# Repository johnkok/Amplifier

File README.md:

# Amplifier
This is an amplifier project, inluding both software sources for CPU/DSP and also hardware design files.

# folders
**fw:** includes the ST32F407 CPU firmware<br />
**DSP:** includes the ADAU1497 design files<br />
**amp_board:** includes the kicad design foles for the audio power amplifier board<br />
**cntrl_board:** includes the controller board kicad design files<br />
**3d:** 3d printer freecad files<br />

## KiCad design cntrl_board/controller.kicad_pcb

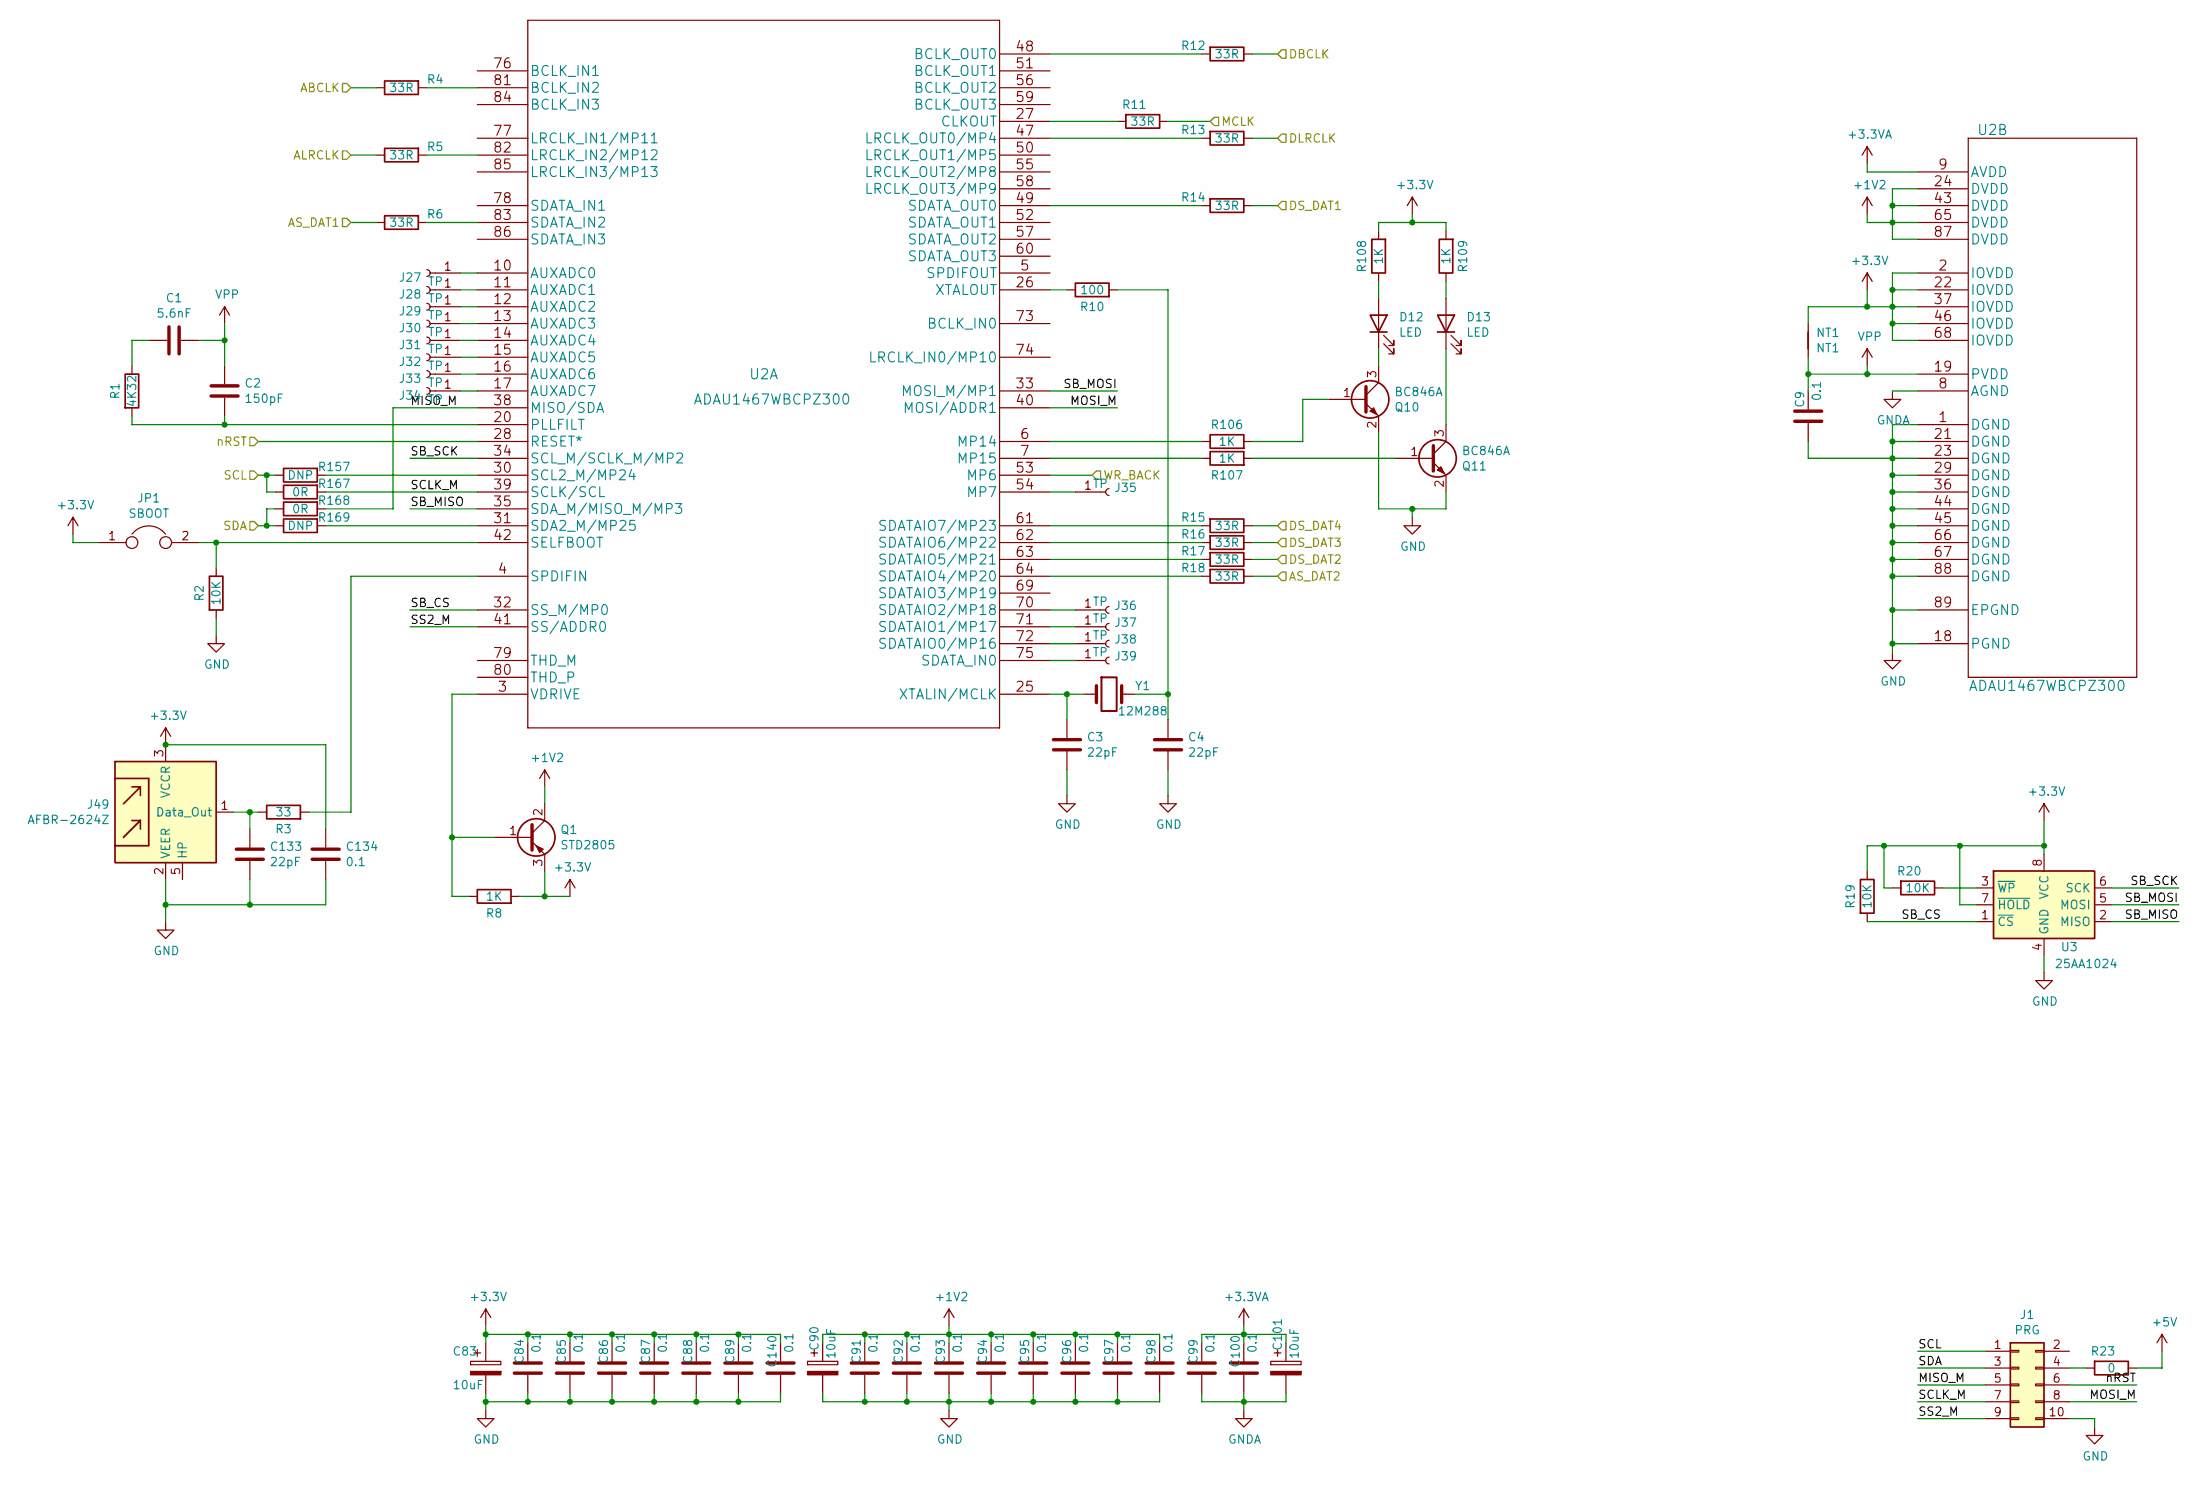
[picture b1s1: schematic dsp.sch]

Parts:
C1: 5.6nF; C_0603_1608Metric_Pad1.08x0.95mm_HandSolder
C2: 150pF; C_0603_1608Metric_Pad1.08x0.95mm_HandSolder
C3, C4, C133: 22pF; C_0603_1608Metric_Pad1.08x0.95mm_HandSolder
C9, C84, C85, C86, C87, C88, C89, C91, C92, C93, C94, C95, C96, C97, C98, C99, C100, C134, C140: 0.1; C_0603_1608Metric_Pad1.08x0.95mm_HandSolder
C83, C90, C101: 10uF; CP_Elec_5x5.8
D12, D13: LED; LED_0603_1608Metric_Pad1.05x0.95mm_HandSolder
J1: PRG; IDC-Header_2x05_P2.54mm_Vertical
J27, J28, J29, J30, J31, J32, J33, J34, J35, J36, J37, J38, J39: TP; TestPoint_Keystone_5000-5004_Miniature
J49: AFBR-2624Z; TOSLINK
JP1: SBOOT; PinHeader_1x02_P2.54mm_Vertical
NT1: NT1; NetTie-2_SMD_Pad0.5mm
Q1: STD2805; TO-252-3_TabPin2
Q10, Q11: BC846A; SOT-23
R1: 4K32; R_0603_1608Metric_Pad0.98x0.95mm_HandSolder
R2, R19, R20: 10K; R_0603_1608Metric_Pad0.98x0.95mm_HandSolder
R3: 33; R_0603_1608Metric_Pad0.98x0.95mm_HandSolder
R4, R5, R6, R11, R12, R13, R14, R15, R16, R17, R18: 33R; R_0603_1608Metric_Pad0.98x0.95mm_HandSolder
R8, R106, R107, R108, R109: 1K; R_0603_1608Metric_Pad0.98x0.95mm_HandSolder
R10: 100; R_0603_1608Metric_Pad0.98x0.95mm_HandSolder
R23: 0; R_0603_1608Metric_Pad0.98x0.95mm_HandSolder
R157, R169: DNP; R_0603_1608Metric_Pad0.98x0.95mm_HandSolder
R167, R168: 0R; R_0603_1608Metric_Pad0.98x0.95mm_HandSolder
U2: ADAU1467WBCPZ300
U3: 25AA1024; SOIJ-8_5.3x5.3mm_P1.27mm
Y1: 12M288; Crystal_HC49-U_Vertical

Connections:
+1V2: C90.1, C91.1, C92.1, C93.1, C94.1, C95.1, C96.1, C97.1, C98.1, Q1.2 (C), U2.24 (DVDD), U2.43 (DVDD), U2.65 (DVDD), U2.87 (DVDD)
+3.3VA: C99.1, C100.1, C101.1, U2.9 (AVDD); also elsewhere on the board
+5V: R23.1; also elsewhere on the board
/codec/ABCLK: R4.1; also elsewhere on the board
/codec/ALRCLK: R5.1; also elsewhere on the board
/codec/AS_DAT1: R6.1; also elsewhere on the board
/codec/AS_DAT2: R18.1; also elsewhere on the board
/codec/DBCLK: R12.1; also elsewhere on the board
/codec/DLRCLK: R13.1; also elsewhere on the board
/codec/DS_DAT1: R14.1; also elsewhere on the board
/codec/DS_DAT2: R17.1; also elsewhere on the board
/codec/DS_DAT3: R16.1; also elsewhere on the board
/codec/DS_DAT4: R15.1; also elsewhere on the board
/codec/MCLK: R11.1; also elsewhere on the board
/codec/nRST: J1.6, U2.28 (RESET*); also elsewhere on the board
/dsp/MISO_M: J1.5, R168.2, U2.38 (MISO/SDA)
/dsp/MOSI_M: J1.8, U2.40 (MOSI/ADDR1)
/dsp/SB_CS: R19.2, U2.32 (SS_M/MP0), U3.1 (~CS)
/dsp/SB_MISO: U2.35 (SDA_M/MISO_M/MP3), U3.2 (MISO)
/dsp/SB_MOSI: U2.33 (MOSI_M/MP1), U3.5 (MOSI)
/dsp/SB_SCK: U2.34 (SCL_M/SCLK_M/MP2), U3.6 (SCK)
/dsp/SCLK_M: J1.7, R167.2, U2.39 (SCLK/SCL)
/dsp/SS2_M: J1.9, U2.41 (SS/ADDR0)
/dsp/WR_BACK: U2.53 (MP6); also elsewhere on the board
/ucu/DSP_SCL: J1.1, R157.1, R167.1; also elsewhere on the board
/ucu/DSP_SDA: J1.3, R168.1, R169.1; also elsewhere on the board
GND: C3.2, C4.2, C9.2, C83.2, C84.2, C85.2, C86.2, C87.2, C88.2, C89.2, C90.2, C91.2, C92.2, C93.2, C94.2, C95.2, C96.2, C97.2, C98.2, C133.2, C134.2, C140.2, J1.10, J49.2 (VEER), Q10.2 (E), Q11.2 (E), R2.2, U2.1 (DGND), U2.18 (PGND), U2.21 (DGND), U2.23 (DGND), U2.29 (DGND), U2.36 (DGND), U2.44 (DGND), U2.45 (DGND), U2.66 (DGND), U2.67 (DGND), U2.88 (DGND), U2.89 (EPGND), U3.4 (GND); also elsewhere on the board
GNDA: C99.2, C100.2, C101.2, U2.8 (AGND); also elsewhere on the board
unnamed: C1.1, R1.1
unnamed: C2.1, R1.2, U2.20 (PLLFILT)
unnamed: C3.1, U2.25 (XTALIN/MCLK), Y1.1
unnamed: C4.1, R10.2, Y1.2
unnamed: C133.1, J49.1 (Data_Out), R3.1
unnamed: D12.1 (K), Q10.3 (C)
unnamed: D12.2 (A), R108.1
unnamed: D13.1 (K), Q11.3 (C)
unnamed: D13.2 (A), R109.1
unnamed: J1.4, R23.2
unnamed: J27.1, U2.10 (AUXADC0)
unnamed: J28.1, U2.11 (AUXADC1)
unnamed: J29.1, U2.12 (AUXADC2)
unnamed: J30.1, U2.13 (AUXADC3)
unnamed: J31.1, U2.14 (AUXADC4)
unnamed: J32.1, U2.15 (AUXADC5)
unnamed: J33.1, U2.16 (AUXADC6)
unnamed: J34.1, U2.17 (AUXADC7)
unnamed: J35.1, U2.54 (MP7)
unnamed: J36.1, U2.70 (SDATAIO2/MP18)
unnamed: J37.1, U2.71 (SDATAIO1/MP17)
unnamed: J38.1, U2.72 (SDATAIO0/MP16)
unnamed: J39.1, U2.75 (SDATA_IN0)
unnamed: JP1.2, R2.1, U2.42 (SELFBOOT)
unnamed: Q1.1 (B), R8.1, U2.3 (VDRIVE)
unnamed: Q10.1 (B), R106.2
unnamed: Q11.1 (B), R107.2
unnamed: R3.2, U2.4 (SPDIFIN)
unnamed: R4.2, U2.81 (BCLK_IN2)
unnamed: R5.2, U2.82 (LRCLK_IN2/MP12)
unnamed: R6.2, U2.83 (SDATA_IN2)
unnamed: R10.1, U2.26 (XTALOUT)
unnamed: R11.2, U2.27 (CLKOUT)
unnamed: R12.2, U2.48 (BCLK_OUT0)
unnamed: R13.2, U2.47 (LRCLK_OUT0/MP4)
unnamed: R14.2, U2.49 (SDATA_OUT0)
unnamed: R15.2, U2.61 (SDATAIO7/MP23)
unnamed: R16.2, U2.62 (SDATAIO6/MP22)
unnamed: R17.2, U2.63 (SDATAIO5/MP21)
unnamed: R18.2, U2.64 (SDATAIO4/MP20)
unnamed: R20.1, U3.3 (~WP)
unnamed: R106.1, U2.6 (MP14)
unnamed: R107.1, U2.7 (MP15)
unnamed: R157.2, U2.30 (SCL2_M/MP24)
unnamed: R169.2, U2.31 (SDA2_M/MP25)
VPP: C1.2, C2.2, C9.1, NT1.1, U2.19 (PVDD)

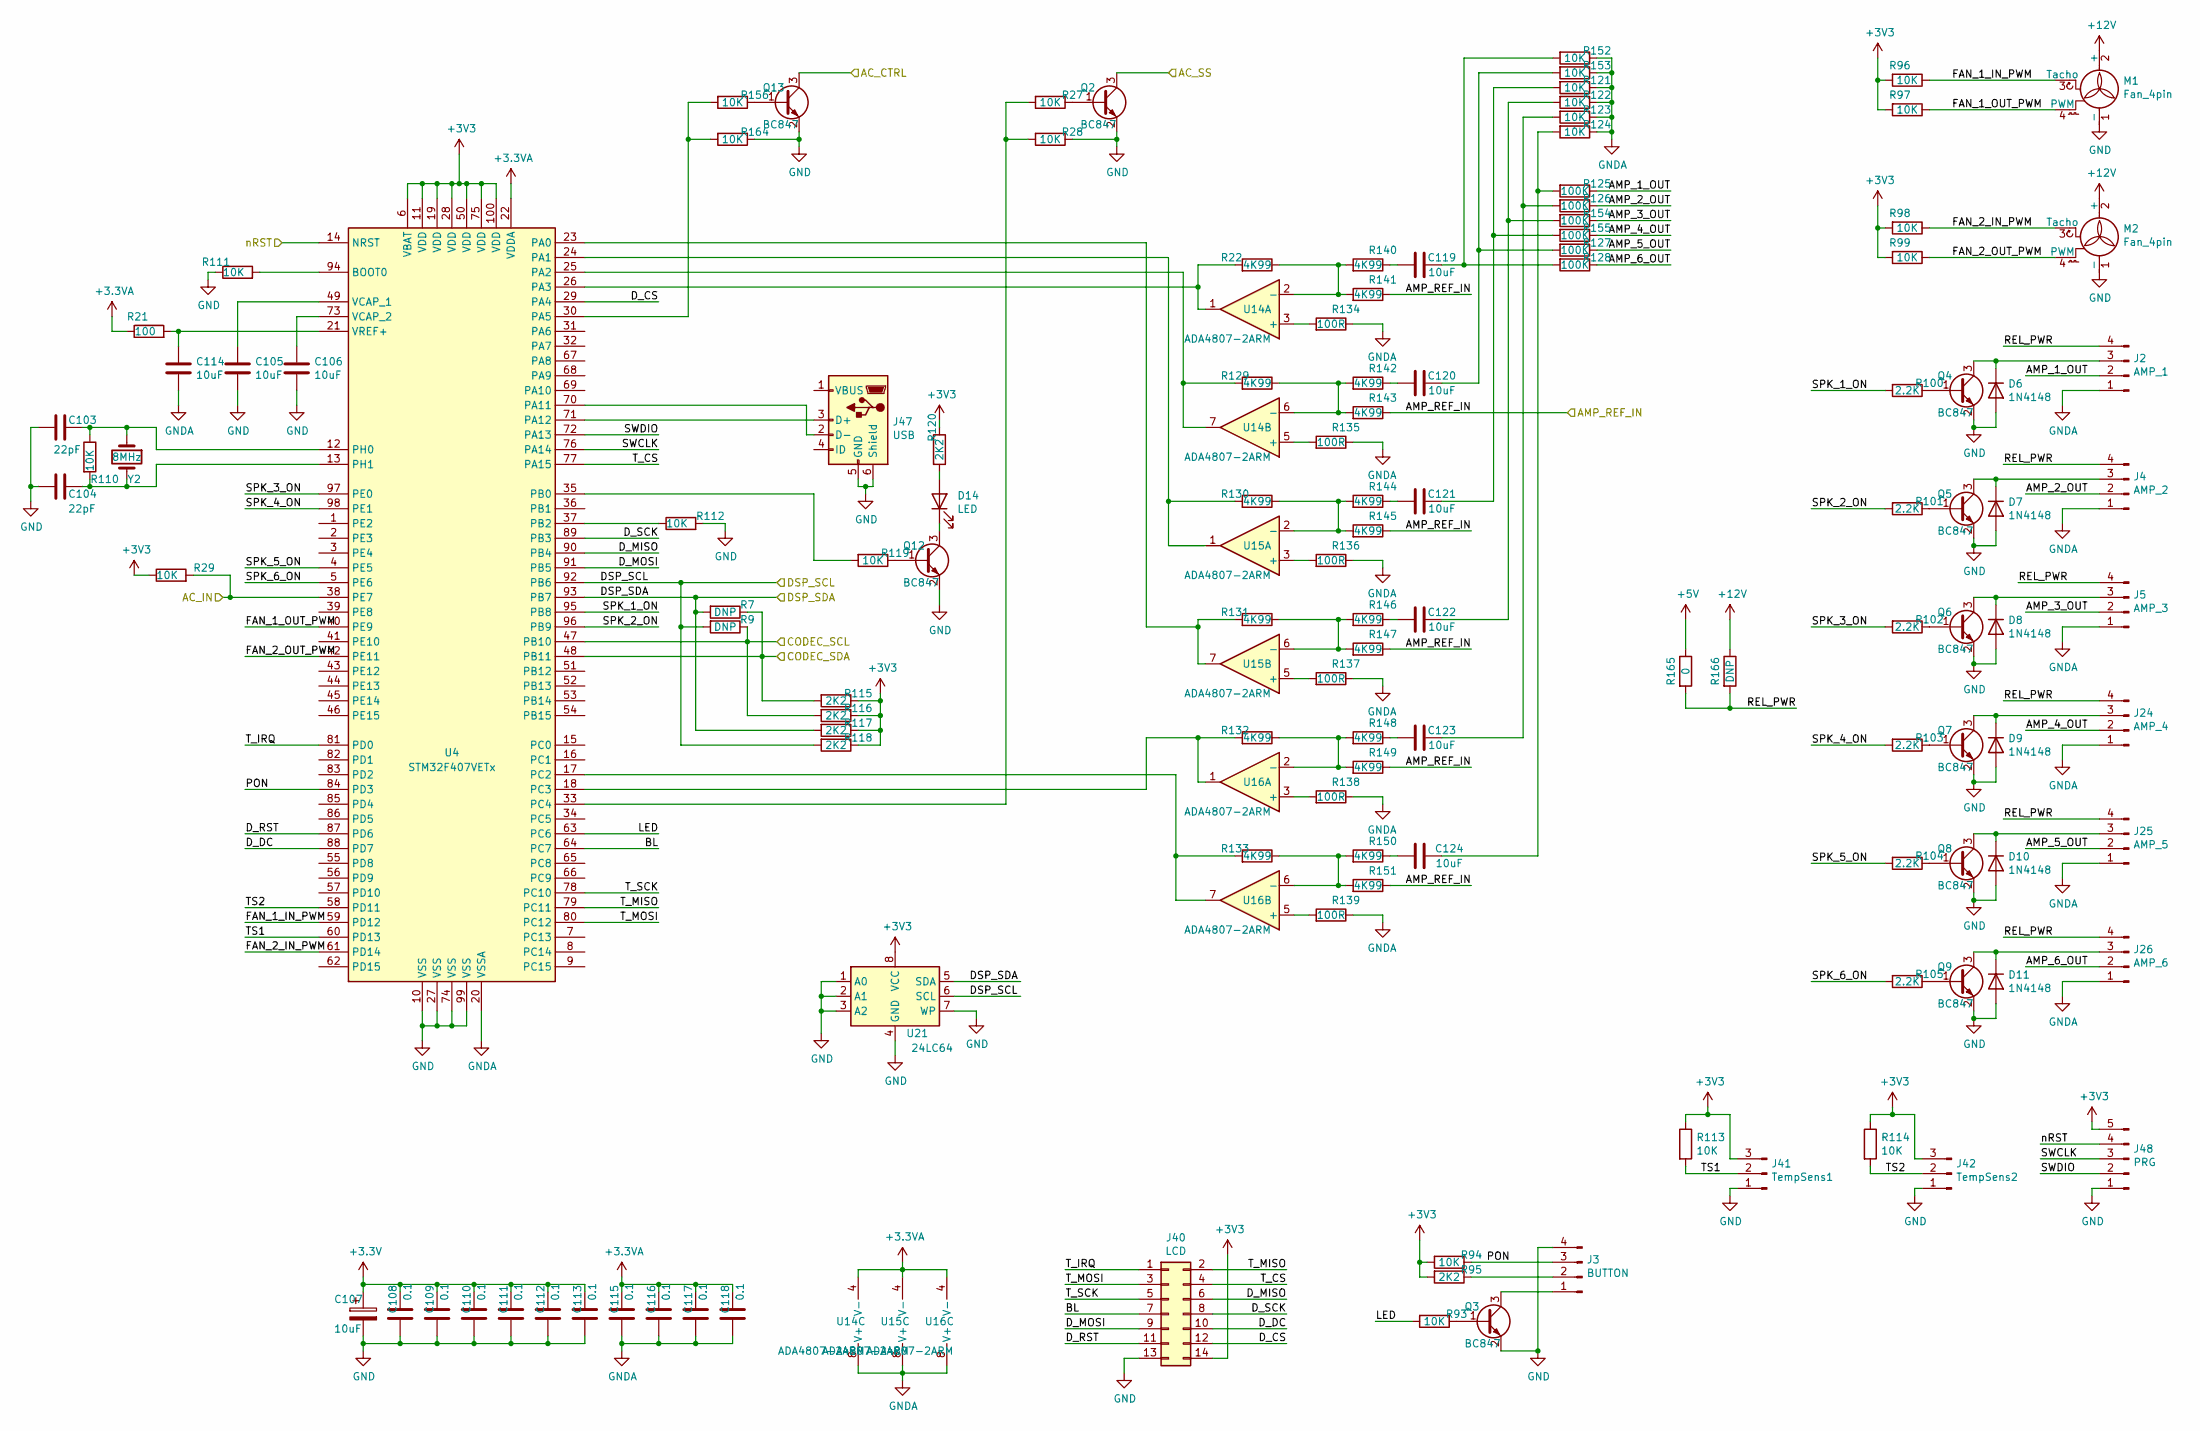
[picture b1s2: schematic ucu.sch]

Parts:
C103, C104: 22pF; R_0603_1608Metric_Pad0.98x0.95mm_HandSolder
C105, C106, C114, C119, C120, C121, C122, C123, C124: 10uF; C_0805_2012Metric_Pad1.18x1.45mm_HandSolder
C107: 10uF; CP_Elec_5x5.8
C108, C109, C110, C111, C112, C113, C115, C116, C117, C118: 0.1; C_0603_1608Metric_Pad1.08x0.95mm_HandSolder
D6, D7, D8, D9, D10, D11: 1N4148; D_SOD-323_HandSoldering
D14: LED; LED_0603_1608Metric_Pad1.05x0.95mm_HandSolder
J2: AMP_1; PinHeader_1x04_P1.27mm_Vertical
J3: BUTTON; PinHeader_1x04_P2.54mm_Vertical
J4: AMP_2; PinHeader_1x04_P1.27mm_Vertical
J5: AMP_3; PinHeader_1x04_P1.27mm_Vertical
J24: AMP_4; PinHeader_1x04_P1.27mm_Vertical
J25: AMP_5; PinHeader_1x04_P1.27mm_Vertical
J26: AMP_6; PinHeader_1x04_P1.27mm_Vertical
J40: LCD; PinSocket_2x07_P2.54mm_Vertical
J41: TempSens1; PinHeader_1x03_P2.54mm_Vertical
J42: TempSens2; PinHeader_1x03_P2.54mm_Vertical
J47: USB; USB_Micro-B_Molex-105017-0001
J48: PRG; PinSocket_1x05_P2.54mm_Vertical
M1, M2: Fan_4pin; PinHeader_1x04_P2.54mm_Vertical
Q2, Q3, Q4, Q5, Q6, Q7, Q8, Q9, Q12, Q13: BC847; SOT-23
R7, R9: DNP; R_0603_1608Metric_Pad0.98x0.95mm_HandSolder
R21: 100; R_0603_1608Metric_Pad0.98x0.95mm_HandSolder
R22, R129, R130, R131, R132, R133, R140, R141, R142, R143, R144, R145, R146, R147, R148, R149, R150, R151: 4K99; R_0603_1608Metric_Pad0.98x0.95mm_HandSolder
R27, R28, R29, R93, R94, R96, R97, R98, R99, R110, R111, R112, R113, R114, R119, R121, R122, R123, R124, R152, R153, R156, R164: 10K; R_0603_1608Metric_Pad0.98x0.95mm_HandSolder
R95, R115, R116, R117, R118, R120: 2K2; R_0603_1608Metric_Pad0.98x0.95mm_HandSolder
R100, R101, R102, R103, R104, R105: 2.2K; R_0603_1608Metric_Pad0.98x0.95mm_HandSolder
R125, R126, R127, R128, R154, R155: 100K; R_0603_1608Metric_Pad0.98x0.95mm_HandSolder
R134, R135, R136, R137, R138, R139: 100R; R_0603_1608Metric_Pad0.98x0.95mm_HandSolder
R165: 0; R_1206_3216Metric_Pad1.30x1.75mm_HandSolder
R166: DNP; R_1206_3216Metric_Pad1.30x1.75mm_HandSolder
U4: STM32F407VETx; LQFP-100_14x14mm_P0.5mm
U14, U15, U16: ADA4807-2ARM; MSOP-8_3x3mm_P0.65mm
U21: 24LC64; SO-8_3.9x4.9mm_P1.27mm
Y2: 8MHz; Crystal_HC49-4H_Vertical

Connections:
+3.3VA: C115.1, C116.1, C117.1, C118.1, R21.1, U4.22 (VDDA), U14.4 (V-), U15.4 (V-), U16.4 (V-); also elsewhere on the board
+5V: R165.1; also elsewhere on the board
+12V: M1.2 (+), M2.2 (+), R166.1; also elsewhere on the board
/codec/AMP_REF_IN: R141.1, R143.1, R145.1, R147.1, R149.1, R151.1; also elsewhere on the board
/codec/nRST: J48.4, U4.14 (NRST); also elsewhere on the board
/ucu/AC_CTRL: Q13.3 (C); also elsewhere on the board
/ucu/AC_IN: R29.2, U4.38 (PE7); also elsewhere on the board
/ucu/AC_SS: Q2.3 (C); also elsewhere on the board
/ucu/AMP_1_OUT: J2.2, R125.1
/ucu/AMP_2_OUT: J4.2, R126.1
/ucu/AMP_3_OUT: J5.2, R154.1
/ucu/AMP_4_OUT: J24.2, R155.1
/ucu/AMP_5_OUT: J25.2, R127.1
/ucu/AMP_6_OUT: J26.2, R128.1
/ucu/BL: J40.7, U4.64 (PC7)
/ucu/CODEC_SCL: R9.1, R116.2, U4.47 (PB10); also elsewhere on the board
/ucu/CODEC_SDA: R7.1, R115.2, U4.48 (PB11); also elsewhere on the board
/ucu/DSP_SCL: R9.2, R118.2, U4.92 (PB6), U21.6 (SCL); also elsewhere on the board
/ucu/DSP_SDA: R7.2, R117.2, U4.93 (PB7), U21.5 (SDA); also elsewhere on the board
/ucu/D_CS: J40.12, U4.29 (PA4)
/ucu/D_DC: J40.10, U4.88 (PD7)
/ucu/D_MISO: J40.6, U4.90 (PB4)
/ucu/D_MOSI: J40.9, U4.91 (PB5)
/ucu/D_RST: J40.11, U4.87 (PD6)
/ucu/D_SCK: J40.8, U4.89 (PB3)
/ucu/FAN_1_IN_PWM: M1.3 (Tacho), R96.1, U4.59 (PD12)
/ucu/FAN_1_OUT_PWM: M1.4 (PWM), R97.1, U4.40 (PE9)
/ucu/FAN_2_IN_PWM: M2.3 (Tacho), R98.1, U4.61 (PD14)
/ucu/FAN_2_OUT_PWM: M2.4 (PWM), R99.1, U4.42 (PE11)
/ucu/LED: R93.2, U4.63 (PC6)
/ucu/PON: J3.3, R94.1, U4.84 (PD3)
/ucu/REL_PWR: J2.4, J4.4, J5.4, J24.4, J25.4, J26.4, R165.2, R166.2
/ucu/SPK_1_ON: R100.2, U4.95 (PB8)
/ucu/SPK_2_ON: R101.2, U4.96 (PB9)
/ucu/SPK_3_ON: R102.2, U4.97 (PE0)
/ucu/SPK_4_ON: R103.2, U4.98 (PE1)
/ucu/SPK_5_ON: R104.2, U4.4 (PE5)
/ucu/SPK_6_ON: R105.2, U4.5 (PE6)
/ucu/SWCLK: J48.3, U4.76 (PA14)
/ucu/SWDIO: J48.2, U4.72 (PA13)
/ucu/TS1: J41.2, R113.2, U4.60 (PD13)
/ucu/TS2: J42.2, R114.2, U4.58 (PD11)
/ucu/T_CS: J40.4, U4.77 (PA15)
/ucu/T_IRQ: J40.1, U4.81 (PD0)
/ucu/T_MISO: J40.2, U4.79 (PC11)
/ucu/T_MOSI: J40.3, U4.80 (PC12)
/ucu/T_SCK: J40.5, U4.78 (PC10)
GND: C103.2, C104.2, C105.2, C106.2, C107.2, C108.2, C109.2, C110.2, C111.2, C112.2, C113.2, D6.2 (A), D7.2 (A), D8.2 (A), D9.2 (A), D10.2 (A), D11.2 (A), J3.4, J40.13, J41.1, J42.1, J47.5 (GND), J47.6 (Shield), J48.1, M1.1 (-), M2.1 (-), Q2.2 (E), Q3.2 (E), Q4.2 (E), Q5.2 (E), Q6.2 (E), Q7.2 (E), Q8.2 (E), Q9.2 (E), Q12.2 (E), Q13.2 (E), R28.1, R111.1, R112.2, R164.1, U4.10 (VSS), U4.27 (VSS), U4.74 (VSS), U4.99 (VSS), U21.1 (A0), U21.2 (A1), U21.3 (A2), U21.4 (GND), U21.7 (WP); also elsewhere on the board
GNDA: C114.2, C115.2, C116.2, C117.2, C118.2, J2.1, J4.1, J5.1, J24.1, J25.1, J26.1, R121.1, R122.1, R123.1, R124.1, R134.1, R135.1, R136.1, R137.1, R138.1, R139.1, R152.1, R153.1, U4.20 (VSSA), U14.8 (V+), U15.8 (V+), U16.8 (V+); also elsewhere on the board
unnamed: C103.1, R110.1, U4.12 (PH0), Y2.1
unnamed: C104.1, R110.2, U4.13 (PH1), Y2.2
unnamed: C105.1, U4.49 (VCAP_1)
unnamed: C106.1, U4.73 (VCAP_2)
unnamed: C114.1, R21.2, U4.21 (VREF+)
unnamed: C119.1, R140.1
unnamed: C119.2, R128.2, R152.2
unnamed: C120.1, R142.1
unnamed: C120.2, R127.2, R153.2
unnamed: C121.1, R144.1
unnamed: C121.2, R121.2, R155.2
unnamed: C122.1, R146.1
unnamed: C122.2, R122.2, R154.2
unnamed: C123.1, R148.1
unnamed: C123.2, R123.2, R126.2
unnamed: C124.1, R150.1
unnamed: C124.2, R124.2, R125.2
unnamed: D6.1 (K), J2.3, Q4.3 (C)
unnamed: D7.1 (K), J4.3, Q5.3 (C)
unnamed: D8.1 (K), J5.3, Q6.3 (C)
unnamed: D9.1 (K), J24.3, Q7.3 (C)
unnamed: D10.1 (K), J25.3, Q8.3 (C)
unnamed: D11.1 (K), J26.3, Q9.3 (C)
unnamed: D14.1 (K), Q12.3 (C)
unnamed: D14.2 (A), R120.2
unnamed: J3.1, Q3.3 (C)
unnamed: J3.2, R95.1
unnamed: J47.2 (D-), U4.70 (PA11)
unnamed: J47.3 (D+), U4.71 (PA12)
unnamed: Q2.1 (B), R27.1
unnamed: Q3.1 (B), R93.1
unnamed: Q4.1 (B), R100.1
unnamed: Q5.1 (B), R101.1
unnamed: Q6.1 (B), R102.1
unnamed: Q7.1 (B), R103.1
unnamed: Q8.1 (B), R104.1
unnamed: Q9.1 (B), R105.1
unnamed: Q12.1 (B), R119.1
unnamed: Q13.1 (B), R156.1
unnamed: R22.2, U4.26 (PA3), U14.1
unnamed: R27.2, R28.2, U4.33 (PC4)
unnamed: R111.2, U4.94 (BOOT0)
unnamed: R112.1, U4.37 (PB2)
unnamed: R119.2, U4.35 (PB0)
unnamed: R129.1, R142.2, R143.2, U14.6 (-)
unnamed: R129.2, U4.25 (PA2), U14.7
unnamed: R130.1, R144.2, R145.2, U15.2 (-)
unnamed: R130.2, U4.24 (PA1), U15.1
unnamed: R131.1, R146.2, R147.2, U15.6 (-)
unnamed: R131.2, U4.23 (PA0), U15.7
unnamed: R132.1, R148.2, R149.2, U16.2 (-)
unnamed: R132.2, U4.18 (PC3), U16.1
unnamed: R133.1, R150.2, R151.2, U16.6 (-)
unnamed: R133.2, U4.17 (PC2), U16.7
unnamed: R134.2, U14.3 (+)
unnamed: R135.2, U14.5 (+)
unnamed: R136.2, U15.3 (+)
unnamed: R137.2, U15.5 (+)
unnamed: R138.2, U16.3 (+)
unnamed: R139.2, U16.5 (+)
unnamed: R22.1, R140.2, R141.2, U14.2 (-)
unnamed: R156.2, R164.2, U4.30 (PA5)

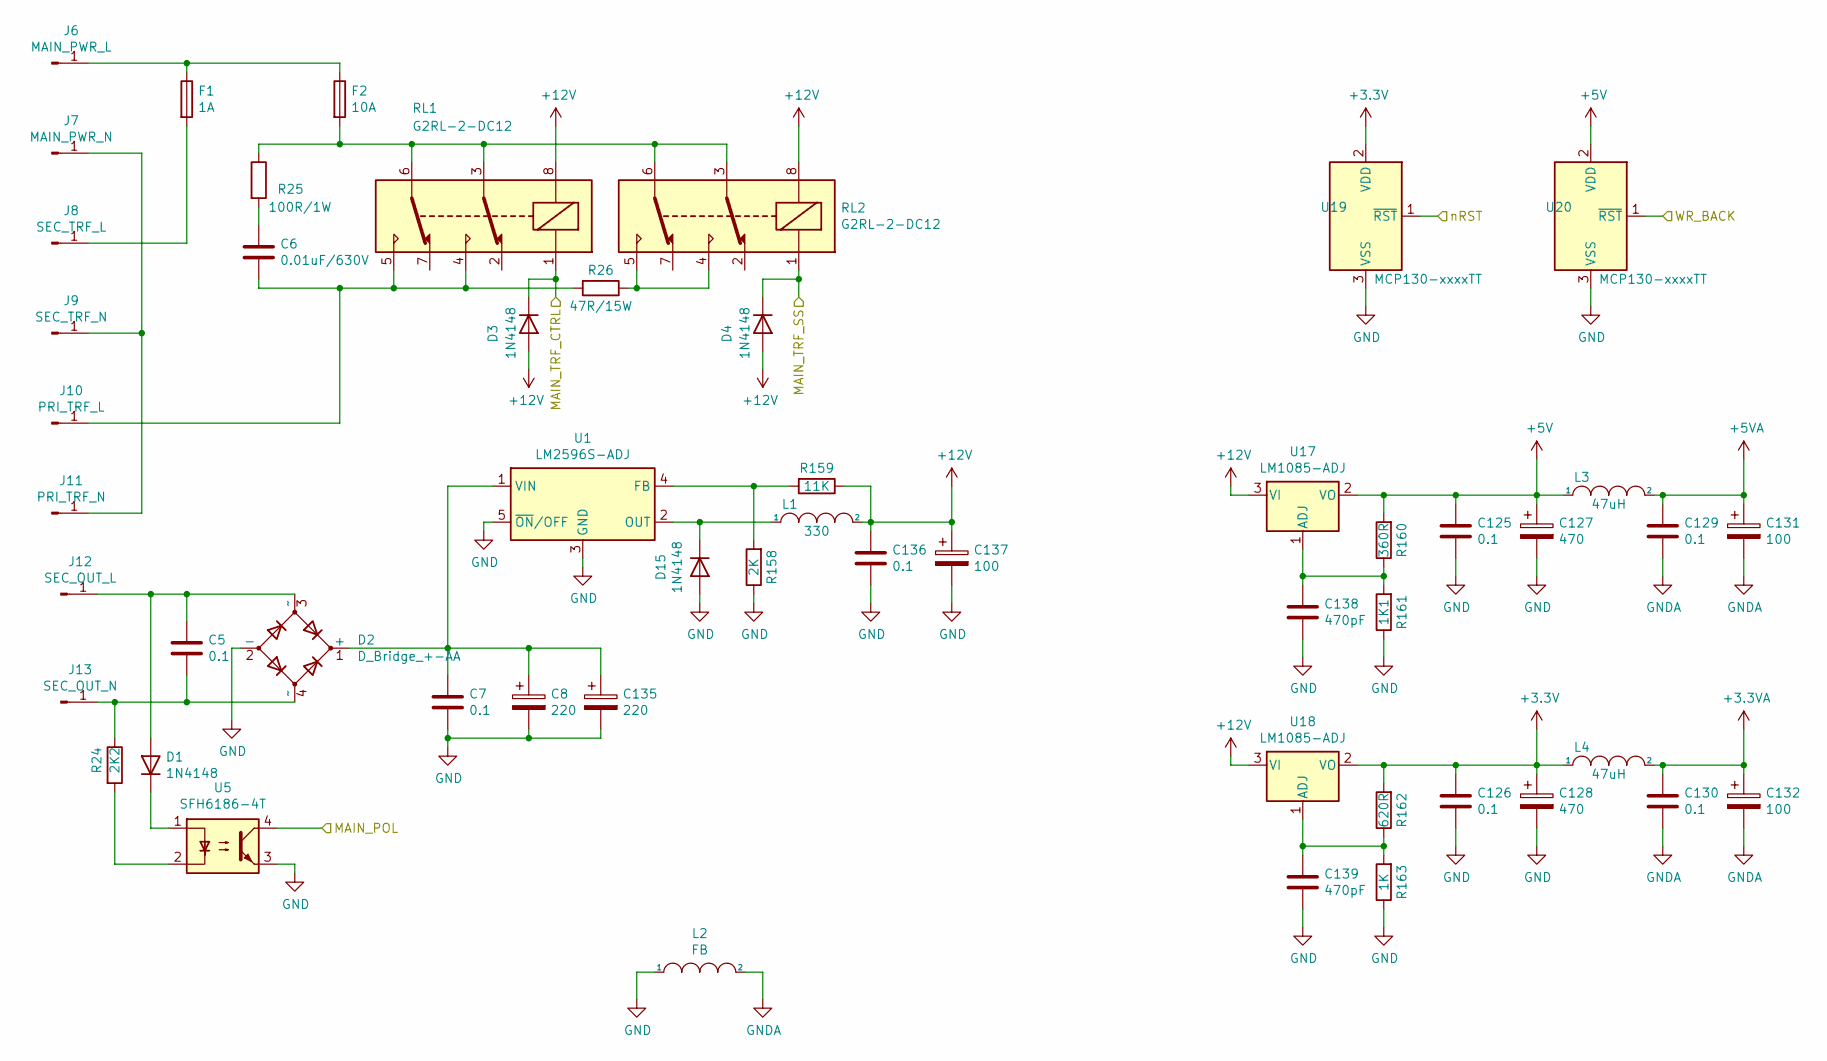
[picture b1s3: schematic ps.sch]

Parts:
C5, C7, C125, C126, C129, C130, C136: 0.1; C_0603_1608Metric_Pad1.08x0.95mm_HandSolder
C6: 0.01uF/630V; C_Disc_D8.0mm_W5.0mm_P10.00mm
C8, C135: 220; CP_Elec_8x6.2
C127, C128: 470; CP_Elec_8x6.5
C131, C132, C137: 100; CP_Elec_6.3x7.7
C138, C139: 470pF; C_0603_1608Metric_Pad1.08x0.95mm_HandSolder
D1, D3, D4, D15: 1N4148; D_SOD-323_HandSoldering
D2: D_Bridge_+-AA; Diode_Bridge_Vishay_DFS
F1: 1A; Fuseholder_Cylinder-5x20mm_Schurter_0031_8201_Horizontal_Op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
F2: 10A; Fuseholder_Cylinder-5x20mm_Schurter_0031_8201_Horizontal_Op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
J6: MAIN_PWR_L; TERMINAL_250
J7: MAIN_PWR_N; TERMINAL_250
J8: SEC_TRF_L; TERMINAL_250
J9: SEC_TRF_N; TERMINAL_250
J10: PRI_TRF_L; TERMINAL_250
J11: PRI_TRF_N; TERMINAL_250
J12: SEC_OUT_L; TERMINAL_250
J13: SEC_OUT_N; TERMINAL_250
L1: 330; L_12x12mm_H4.5mm
L2: FB; L_0805_2012Metric_Pad1.15x1.40mm_HandSolder
L3, L4: 47uH; L_Bourns-SRU8028_8.0x8.0mm
R24: 2K2; R_0603_1608Metric_Pad0.98x0.95mm_HandSolder
R25: 100R/1W; R_Axial_DIN0414_L11.9mm_D4.5mm_P15.24mm_Horizontal
R26: 47R/15W; R_Radial_Power_L13.0mm_W9.0mm_P5.00mm
R158: 2K; R_0603_1608Metric_Pad0.98x0.95mm_HandSolder
R159: 11K; R_0603_1608Metric_Pad0.98x0.95mm_HandSolder
R160: 360R; R_0603_1608Metric_Pad0.98x0.95mm_HandSolder
R161: 1K1; R_0603_1608Metric_Pad0.98x0.95mm_HandSolder
R162: 620R; R_0603_1608Metric_Pad0.98x0.95mm_HandSolder
R163: 1K; R_0603_1608Metric_Pad0.98x0.95mm_HandSolder
RL1, RL2: G2RL-2-DC12; Relay_DPDT_Omron_G2RL
U1: LM2596S-ADJ; TO-263-5_TabPin3
U5: SFH6186-4T; SO-4_7.6x3.6mm_P2.54mm
U17, U18: LM1085-ADJ; TO-263-3_TabPin2
U19, U20: MCP130-xxxxTT; SOT-23

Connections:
+3.3VA: C130.1, C132.1, L4.2; also elsewhere on the board
+5V: C125.1, C127.1, L3.1, R160.2, U17.2 (VO), U20.2 (VDD); also elsewhere on the board
+5VA: C129.1, C131.1, L3.2; also elsewhere on the board
+12V: C136.1, C137.1, D3.2 (A), D4.2 (A), L1.2, R159.1, RL1.8, RL2.8, U17.3 (VI), U18.3 (VI); also elsewhere on the board
/codec/nRST: U19.1 (~RST); also elsewhere on the board
/dsp/WR_BACK: U20.1 (~RST); also elsewhere on the board
/ucu/AC_CTRL: D3.1 (K), RL1.1; also elsewhere on the board
/ucu/AC_IN: U5.4; also elsewhere on the board
/ucu/AC_SS: D4.1 (K), RL2.1; also elsewhere on the board
GND: C7.2, C8.2, C125.2, C126.2, C127.2, C128.2, C135.2, C136.2, C137.2, C138.2, C139.2, D2.2 (-), D15.2 (A), L2.1, R158.1, R161.1, R163.1, U1.3 (GND), U1.5 (~ON~/OFF), U5.3, U19.3 (VSS), U20.3 (VSS); also elsewhere on the board
GNDA: C129.2, C130.2, C131.2, C132.2, L2.2; also elsewhere on the board
unnamed: C5.1, D1.2 (A), D2.3 (~~), J12.1
unnamed: C5.2, D2.4 (~~), J13.1, R24.1
unnamed: C6.1, R25.2
unnamed: C6.2, J10.1, R26.2, RL1.4, RL1.5
unnamed: C7.1, C8.1, C135.1, D2.1 (+), U1.1 (VIN)
unnamed: C138.1, R160.1, R161.2, U17.1 (ADJ)
unnamed: C139.1, R162.1, R163.2, U18.1 (ADJ)
unnamed: D1.1 (K), U5.1
unnamed: D15.1 (K), L1.1, U1.2 (OUT)
unnamed: F1.1, F2.1, J6.1
unnamed: F1.2, J8.1
unnamed: F2.2, R25.1, RL1.3, RL1.6, RL2.3, RL2.6
unnamed: J7.1, J9.1, J11.1
unnamed: R24.2, U5.2
unnamed: R26.1, RL2.4, RL2.5
unnamed: R158.2, R159.2, U1.4 (FB)

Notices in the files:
parts and their libraries:
Copyright 2021 Accelerated Designs. All rights reserved.
